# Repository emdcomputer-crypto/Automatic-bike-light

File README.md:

# Smart Bike Dynamic Lighting System

This is my custom built smart bike lighting system powered by a Seeed Studio XIAO ESP32-S3 and an MPU6050 inertial sensor. I designed this project from scratch to provide safety features on the road including automatic deceleration triggered brake lights, dynamic turn signals, crash detection, and a local Wi-Fi web server that lets me control and monitor everything directly from my phone without needing an internet connection or an external app.

---
# Everything you need

* schematic, pcb and others in `Hardware` 
* Firmware `Firmware` (wich i highly reccomend to make changes to)
* Fabrication files (gerber) `FabricationFiles` needed to produce the pcb 
---

## Core Features

* **Tilt-Compensated Braking:** The system calculates true deceleration using a sort of filter, filtering out false triggers caused by riding up or down hills.
* **Brake time:** Uses independent thresholds to turn the brake light on and off, preventing annoying flickering during gradual slowing.
* **Turn Signal effect:** Cool and progressive sliding animations across the side LEDs when turning wich i really like.
* **Crash Detection (SOS):** Automatically monitors for severe impacts or vehicle rollovers, triggering a Morse code SOS beacon (`... --- ...`) in an emergency. (Random feature honestly but still cool)
* **Local Wi-Fi Web Server:** The ESP32 hosts a local hotspot serving a dashboard for live data showing the lights state and the possibility of different modes with also a manual customization mode wich lets you customize wich leds stay on (The mode will always go back to "auto" after every 2 minutes, of course you can change that).

---

## Hardware & PCB Design

I designed a custom PCB in KiCad measuring 120x35 mm with rounded edges (2mm diametre) and two mounting holes in opposite corners for securing it in any custom 3d printed enclosure

### Component Breakdown
* **Microcontroller:** Seeed Studio XIAO ESP32-S3 (chosen for its size and built-in Wi-Fi).
* **Inertial Sensor:** MPU6050 6-axis accelerometer and gyroscope.
* **LEDs  (Rear View Layout):**
  * **Left Turn Indicator:** 3 yellow LEDs (`LEFT1`, `LEFT2`, `LEFT3`).
  * **Brake Lights:** 4 red LEDs (`BRAKE1`, `BRAKE2`, `BRAKE3`, `BRAKE4`). *Note: Due to pin constraints on the XIAO, brake LEDs 3 and 4 share a single control pin in the original firware when testing it was made for the full size esp32 wich may lead to bugs in the firmware.*
  * **Right Turn Indicator:** 3 yellow LEDs (`RIGHT1`, `RIGHT2`, `RIGHT3`).
* **Power Management:** LiPo battery connected via a 2-pin header paired with a USB-C charging circuit is the best option.

### PCB Layout Strategy
I routed the entire board and placed the XIAO ESP32-S3, the MPU6050 header, and the battery connector flipped onto the **back layer**. This left plenty of space on the front layer exclusively for all 10 LEDs. I added custom icons on the silkscreen, poured a solid GND copper plane across the bottom layer for signal integrity, and completed the layout with 0 DRC errors.

---

# Bill of Materials (BOM)

| Category / Role | Item | Qty | Price | Link |
| :--- | :--- | :--- | :--- | :--- |
| **Microcontroller** | Seeed Studio XIAO ESP32-S3 | 1 | $7.28 | [Aliexpress](https://it.aliexpress.com/item/1005006987905528.html?spm=a2g0o.cart.0.0.4b9e18fcb14mQg&mp=1&pdp_npi=6%40dis%21USD%21USD+22.06%21USD+7.28%21%21USD+7.28%21%21%21%400b88a96117943407415205840e0c3f%2112000056625194546%21ct%21IT%218194849047%21%211%210%21&gatewayAdapt=glo2ita) |
| **Boost Converter** | the mt3608 | 1 | $1.45 | [Aliexpress](https://it.aliexpress.com/item/1005006361814667.html?spm=a2g0o.cart.0.0.4b9e18fcb14mQg&mp=1&pdp_npi=6%40dis%21USD%21USD+1.51%21USD+1.45%21%21USD+1.45%21%21%21%400b88a96117943407415205840e0c3f%2112000036895232308%21ct%21IT%218194849047%21%211%210%21&gatewayAdapt=glo2ita) |
| **Battery Charger** | tp4056 | 1 | $1.35 | [Aliexpress](https://it.aliexpress.com/item/1005007355163444.html?spm=a2g0o.cart.0.0.4b9e18fcb14mQg&mp=1&pdp_npi=6%40dis%21USD%21USD+1.36%21USD+1.35%21%21USD+1.35%21%21%21%400b88a96117943407415205840e0c3f%2112000040398749961%21ct%21IT%218194849047%21%211%210%21&gatewayAdapt=glo2ita) |
| **Battery** | 3.7V 1800mAh LiPo Rechargeable Battery | 1 | $15.03 | [Amazon](https://www.amazon.it/dp/B08ZCQXFX4?psc=1&ref_=cm_sw_r_cp_ud_ct_YRPRFCPGAK7MDH9JT337_4) |
| **Inertial Sensor** | Mpu6050 | 1 | $2.62 | [Aliexpress](https://it.aliexpress.com/item/641898763.html?spm=a2g0o.cart.0.0.4b9e18fcb14mQg&mp=1&pdp_npi=6%40dis%21USD%21USD+2.78%21USD+2.62%21%21USD+2.62%21%21%21%400b88a96117943407415205840e0c3f%2158518793197%21ct%21IT%218194849047%21%211%210%21&gatewayAdapt=glo2ita) |
| **LEDs & Resistors** | A cheap kit containing some resistors and leds | 1 kit | $3.38 | [Aliexpress](https://it.aliexpress.com/item/1005007492471456.html?spm=a2g0o.cart.0.0.4b9e18fcb14mQg&mp=1&pdp_npi=6%40dis%21USD%21USD+12.49%21USD+3.38%21%21USD+3.38%21%21%21%400b88a96117943407415205840e0c3f%2112000041009210012%21ct%21IT%218194849047%21%211%210%21&gatewayAdapt=glo2ita) |
| **PCB Fabrication** | JLCPCB Custom PCB Manufacturing (Gerber files in Hardware folder) (this also includes shipping) | 1 | $43.57 | [JLCPCB](https://jlcpcb.com) |

### AliExpress total (items, shipping, and estimated import fees): **$57.13 USD**
### JLCPCB total (including shipping): **$43.57 USD**
### Total Estimated: **$100.70 USD**

## Startup Sequence & Behavioral Diagnostics

When I power on the system, it has some simple and usefull sequences before starting:

1. **LED Self-Test:** 
   * Left LEDs -> Brake LEDs -> Right LEDs light up briefly in sequence so we can verify all leds work.
2. **Full Flash:** 
   * All LEDs flash simultaneously to confirm everything is fine.
3. **Sensor Diagnostics:** 
   * 3 yellow flashes indicate whether the MPU6050 is detected. If it fails to get detected it will keep flashing .
4. **initial Calibration:** 
   * Alternating yellow and red lights indicate MPU6050 calibration. I keep the bike completely still during this step to calibrate accelerometer and gyro biases.
5. **Ready Animation:** 
   * A sweeping light sequence from left to right followed by one full flash indicates the system is on everything should work.

---

## Firmware Architecture 

Using the help of AI i wrote a lot of firmwares (still learning c++ in school but can't write full firwmwares so i'm sorry i'm still working and watching tutorials) went thru different bug fixes and all but this was the best most stable one wich still due to the lack of space in the pcb i had to go with a smaller and different microcontroller than the original one (that's why i included the original firmware that was built on the full sized esp32 wrom) so the firmware might be unstable or make some stuff not work either way feel free to take this firmware fix it, customize it or make one from scratch as i will provide the schematic too.

### Phone Controller & Web Dashboard
Connecting to the bike's Wi-Fi hotspot (`SmartBike`) opens a website control dashboard with the following capabilities:
* **Live data:** data for deceleration, pitch, roll, and motion status (`MOVING` / `STILL`).
* **Mode Switching:** the ability to toggle between different preset modes **RIDE AUTO**, **HAZARD**, **MANUAL TEST**, **FLASH ALL**, **CHASE**, and **LIGHTS OFF**.
* **Individual LED Control:** a grid, allowing manual toggling of individual LEDs for testing or for customization.
---

## Getting Started & Requirements

### Required Arduino Libraries
Make sure you have the following libraries installed in your Arduino IDE environment to be able to use the firmware
* `Wire`
* `Adafruit_MPU6050`
* `Adafruit_Sensor`
* `Preferences`
* `WiFi`
* `WebServer`

### Flashing 
1. Open `Code_3.ino` in the Arduino IDE.
2. Select your target board as **Seeed Studio XIAO ESP32-S3** or something similar.
3. Compile and upload the sketch to the board.
4. Open the Serial Monitor at `115200` baud to view boot logs or type `HELP` into the console to use the live serial tuning interface.
5. Connect your phone to the Wi-Fi network `SmartBike` (password: `Bike123`) and on your browser navigate to `http://192.168.4.1`.

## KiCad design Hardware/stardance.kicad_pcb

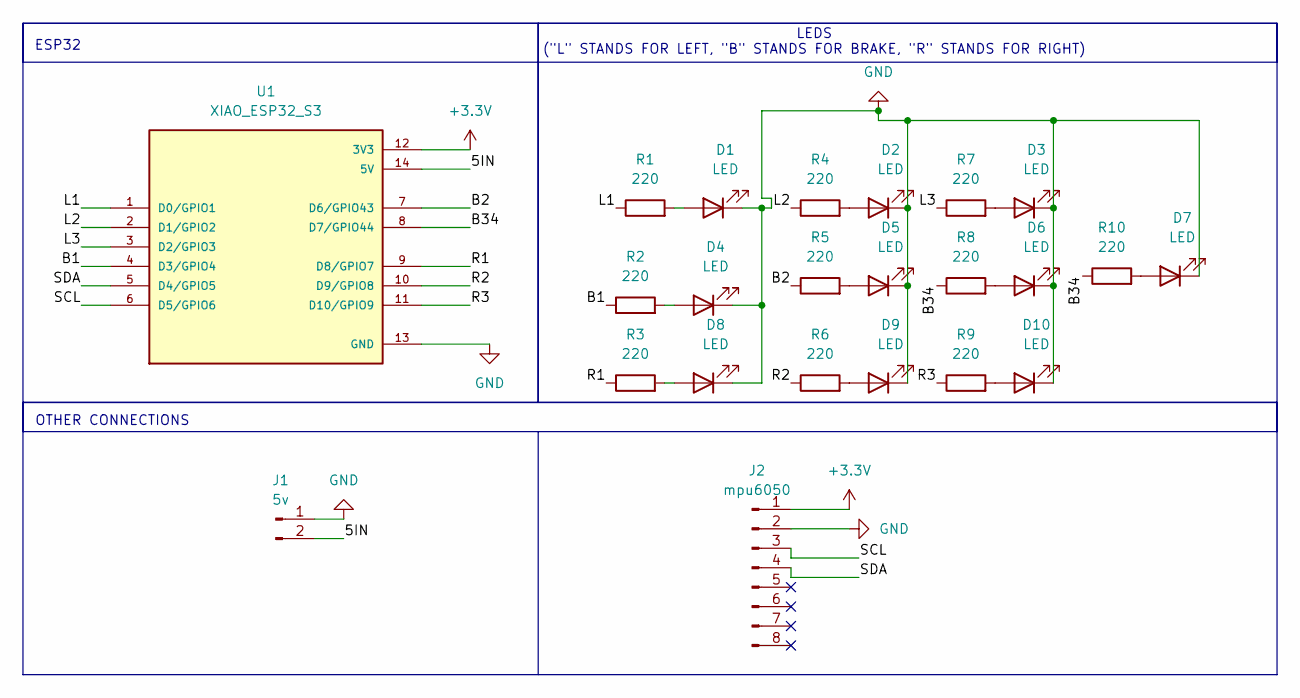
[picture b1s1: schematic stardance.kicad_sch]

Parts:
D1, D2, D3, D4, D5, D6, D7, D8, D9, D10: LED; LED_D5.0mm
J1: 5v; PinHeader_1x02_P2.54mm_Vertical
J2: mpu6050; PinHeader_1x08_P2.54mm_Vertical
R1, R2, R3, R4, R5, R6, R7, R8, R9, R10: 220; R_Axial_DIN0207_L6.3mm_D2.5mm_P7.62mm_Horizontal
U1: XIAO_ESP32_S3; MODULE_XIAO_ESP32_S3; PARTREV April 22nd, 2026

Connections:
+3.3V: J2.1, U1.12 (3V3)
/5IN: J1.2, U1.14 (5V)
/B1: R2.1, U1.4 (D3/GPIO4)
/B2: R5.1, U1.7 (D6/GPIO43)
/B34: R8.1, R10.1, U1.8 (D7/GPIO44)
/L1: R1.1, U1.1 (D0/GPIO1)
/L2: R4.1, U1.2 (D1/GPIO2)
/L3: R7.1, U1.3 (D2/GPIO3)
/R1: R3.1, U1.9 (D8/GPIO7)
/R2: R6.1, U1.10 (D9/GPIO8)
/R3: R9.1, U1.11 (D10/GPIO9)
/SCL: J2.3, U1.6 (D5/GPIO6)
/SDA: J2.4, U1.5 (D4/GPIO5)
GND: D1.1 (K), D2.1 (K), D3.1 (K), D4.1 (K), D5.1 (K), D6.1 (K), D7.1 (K), D8.1 (K), D9.1 (K), D10.1 (K), J1.1, J2.2, U1.13 (GND)
unnamed: D1.2 (A), R1.2
unnamed: D2.2 (A), R4.2
unnamed: D3.2 (A), R7.2
unnamed: D4.2 (A), R2.2
unnamed: D5.2 (A), R5.2
unnamed: D6.2 (A), R8.2
unnamed: D7.2 (A), R10.2
unnamed: D8.2 (A), R3.2
unnamed: D9.2 (A), R6.2
unnamed: D10.2 (A), R9.2

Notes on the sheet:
OTHER CONNECTIONS
ESP32
LEDS ("L" STANDS FOR LEFT, "B" STANDS FOR BRAKE, "R" STANDS FOR RIGHT)

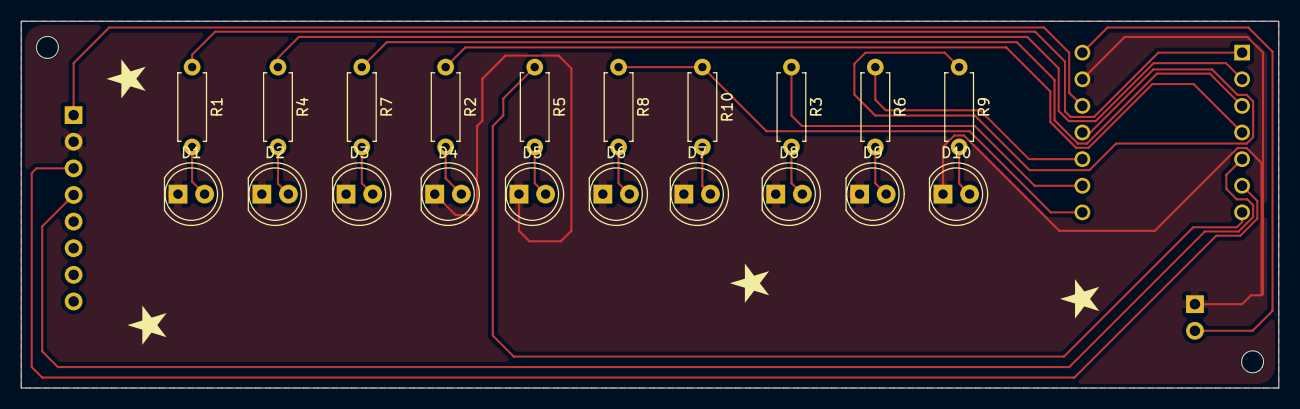
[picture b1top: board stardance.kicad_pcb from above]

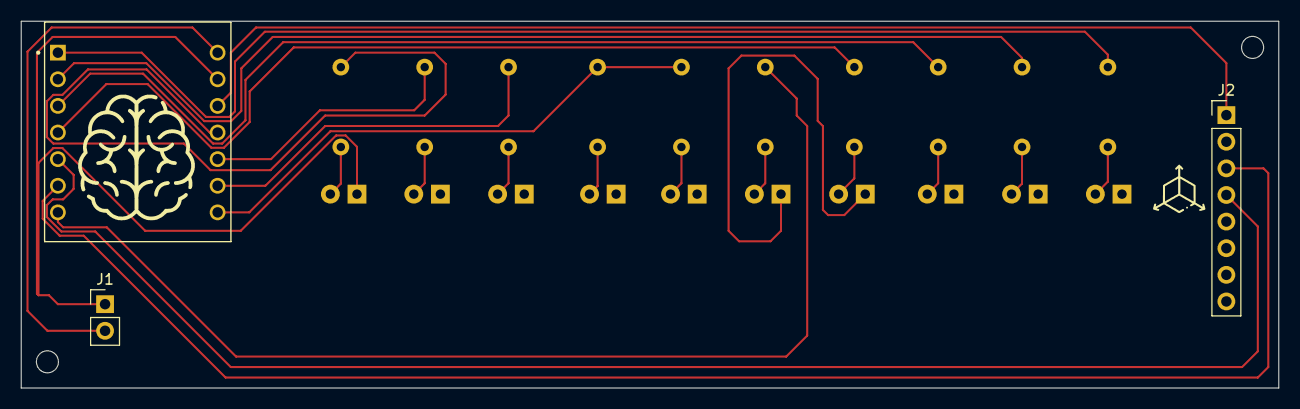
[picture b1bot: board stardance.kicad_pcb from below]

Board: 2 copper layers, 120.0 x 35.0 mm, 23 parts (3 on the bottom side), 24 nets.
